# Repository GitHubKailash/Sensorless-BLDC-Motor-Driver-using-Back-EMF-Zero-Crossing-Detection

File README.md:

# Sensorless BLDC Motor Drive

<p align="center">
  <b>A Low-Cost Sensorless Three-Phase BLDC Motor Controller Using Arduino UNO, IR2104S Gate Drivers, and MOSFET-Based Power Electronics</b>
</p>

---

# Overview

The **Sensorless BLDC Motor Drive** is an Arduino UNO-based three-phase Brushless DC (BLDC) motor controller designed to operate a BLDC motor without requiring external Hall-effect position sensors.

The system uses **Back Electromotive Force (BEMF) zero-crossing detection** to determine the rotor position and perform electronic commutation. An Arduino UNO processes the BEMF signals and generates the required PWM control signals to operate six power MOSFETs through three IR2104S half-bridge gate driver ICs.

The controller implements a six-step electronic commutation technique to drive the three-phase BLDC motor. Motor speed is controlled using PWM, with dedicated push buttons for increasing and decreasing the motor speed.

The project was initially implemented and tested on a perfboard to verify the hardware functionality. Following successful prototype development, the complete motor driver circuit was designed as a PCB using **KiCad**, providing a dedicated hardware implementation.

The project focuses on developing an affordable, compact, and sensorless BLDC motor controller while exploring embedded systems, power electronics, motor control algorithms, and PCB design.

---

# Problem Statement

Conventional sensored BLDC motor controllers require Hall-effect sensors to determine the rotor position for electronic commutation.

Although these sensors provide rotor position information, they increase hardware complexity, wiring requirements, and overall system cost.

This project addresses these limitations by developing a sensorless BLDC motor controller that estimates rotor position using the Back Electromotive Force generated in the motor windings.

By eliminating the need for external rotor position sensors, the system reduces hardware requirements while implementing electronic commutation and PWM-based speed control using an Arduino UNO.

---

# Project Objectives

- Develop a sensorless BLDC motor controller using Arduino UNO.
- Implement BEMF-based rotor position detection.
- Perform six-step electronic commutation.
- Design a three-phase MOSFET inverter circuit.
- Interface IR2104S gate drivers with the Arduino controller.
- Implement PWM-based motor speed control.
- Provide manual speed adjustment using push buttons.
- Develop and test the complete circuit on a perfboard.
- Design a dedicated PCB using KiCad.
- Understand the practical implementation of embedded motor control and power electronics.

---

# Key Features

- Sensorless BLDC motor operation.
- Back EMF zero-crossing detection.
- Six-step electronic commutation.
- Three-phase inverter architecture.
- Arduino UNO-based control system.
- Three IR2104S half-bridge gate drivers.
- Six N-channel power MOSFETs.
- PWM-based speed control.
- Manual speed adjustment using push buttons.
- Open-loop startup sequence.
- Closed-loop BEMF-based commutation after startup.
- Perfboard-based hardware prototype.
- Custom PCB schematic and design using KiCad.

---

# System Architecture

The system consists of an Arduino-based control unit, a three-phase MOSFET inverter, gate driver circuits, and a sensorless BLDC motor.

```text
                  12V DC SUPPLY
                       |
                       |
              +------------------+
              |  Power Inverter  |
              |                  |
              |  6 Power MOSFETs |
              +------------------+
                       |
                       |
              +------------------+
              |  Three-Phase     |
              |  BLDC Motor      |
              +------------------+
                       |
             Phase A, B and C
                       |
                       v
              +------------------+
              |  BEMF Detection  |
              |  Voltage Divider |
              |  Network         |
              +------------------+
                       |
                       v
              +------------------+
              |   Arduino UNO    |
              |   ATmega328P     |
              |                  |
              |  BEMF Detection  |
              |  Commutation     |
              |  PWM Generation  |
              |  Speed Control   |
              +------------------+
                       |
                       v
              +------------------+
              |  IR2104S Gate    |
              |  Driver ICs      |
              +------------------+
                       |
                       v
              +------------------+
              |  MOSFET Switching|
              |  Control         |
              +------------------+
                       |
                       v
                 BLDC Motor
```

### Main System Blocks

| Block | Function |
|---|---|
| Arduino UNO | Main controller and commutation logic |
| BEMF Detection Network | Detects rotor position using motor-generated voltage |
| IR2104S Gate Drivers | Drive high-side and low-side MOSFETs |
| MOSFET Inverter | Converts DC supply into three-phase switched output |
| BLDC Motor | Converts electrical energy into mechanical rotation |
| Speed Control Buttons | Increase and decrease motor speed |

---

# Working Principle

The controller operates using the Back Electromotive Force generated by the three motor windings.

Unlike sensored BLDC controllers, this system does not depend on Hall-effect sensors to determine rotor position.

## 1. Back EMF Generation

When a BLDC motor rotates, its stator windings generate Back Electromotive Force (BEMF).

The three motor phases generate BEMF waveforms that are electrically displaced by 120 degrees.

During six-step commutation:

- Two motor phases are energized.
- One motor phase remains floating.
- The floating phase is monitored for BEMF zero crossing.

The zero-crossing information is used to determine the appropriate time for the next commutation event.

## 2. Virtual Neutral Point Generation

Three resistors are connected to the three motor phases to generate a virtual neutral reference point.

This reference voltage is compared with the BEMF voltage of the floating motor phase.

The voltage divider network reduces the motor phase voltage to a suitable level for the Arduino's detection circuitry.

## 3. BEMF Zero-Crossing Detection

The Arduino UNO uses its internal analog comparator to detect the zero-crossing events.

The comparator compares:

- Positive input: Virtual neutral reference.
- Negative input: Selected floating-phase BEMF signal.

When the floating-phase BEMF crosses the virtual neutral voltage, the comparator output changes state.

The Arduino detects this transition using the analog comparator interrupt.

## 4. Six-Step Electronic Commutation

The motor is controlled using six-step electronic commutation.

During each commutation step, one high-side MOSFET and one low-side MOSFET are activated while the third phase remains floating.

| Step | High-Side MOSFET | Low-Side MOSFET | Floating Phase |
|---|---|---|---|
| 1 | A | B | C |
| 2 | A | C | B |
| 3 | B | C | A |
| 4 | B | A | C |
| 5 | C | A | B |
| 6 | C | B | A |

The sequence repeats continuously to maintain motor rotation.

## 5. Open-Loop Startup

At standstill, the motor does not generate sufficient BEMF for reliable rotor position detection.

Therefore, the controller initially uses an open-loop startup sequence.

During startup:

1. The Arduino initializes the PWM output.
2. A predefined commutation sequence is applied.
3. The commutation interval gradually decreases.
4. The motor accelerates.
5. Once sufficient BEMF is available, the controller enables comparator interrupt-based commutation.

## 6. PWM-Based Speed Control

Motor speed is controlled by adjusting the PWM duty cycle applied to the gate driver control signals.

Two push buttons are provided:

- **Speed Up:** Increases the PWM duty cycle.
- **Speed Down:** Decreases the PWM duty cycle.

The controller maintains the duty cycle within predefined minimum and maximum limits.

---

# Hardware Components

| S.No | Component | Quantity | Purpose |
|---|---|---:|---|
| 1 | Arduino UNO | 1 | Main controller |
| 2 | IR2104S Gate Driver IC | 3 | Half-bridge gate driving |
| 3 | N-Channel Power MOSFET | 6 | Three-phase inverter |
| 4 | 1N4148 Diode | 3 | Bootstrap charging |
| 5 | 33kΩ Resistor | 6 | BEMF sensing and virtual neutral network |
| 6 | 10kΩ Resistor | 3 | Voltage divider network |
| 7 | 100Ω Resistor | 6 | MOSFET gate resistors |
| 8 | 10µF Capacitor | 3 | Gate driver supply decoupling |
| 9 | 2.2µF Capacitor | 3 | Bootstrap capacitors |
| 10 | Push Buttons | 2 | Speed adjustment |
| 11 | BLDC Motor | 1 | Motor load |
| 12 | 12V DC Supply | 1 | Power source |
| 13 | Perfboard | 1 | Prototype implementation |
| 14 | PCB | 1 | Custom circuit implementation |

**Note:** The MOSFET part number should be finalized according to the actual hardware revision. The supplied original reference schematic shows 06N03LA, while your KiCad schematic shows IRF3205.

---

# Controller and Pin Configuration

The Arduino UNO uses its ATmega328P microcontroller for PWM generation, BEMF detection, and motor commutation.

| Arduino Pin | Function |
|---|---|
| D3 | Phase A control |
| D4 | Phase B control |
| D5 | Phase C control |
| D6 | Virtual neutral reference (AIN0) |
| D7 | Phase A BEMF detection (AIN1) |
| A2 | Phase B BEMF detection |
| A3 | Phase C BEMF detection |
| D9 | Phase A gate driver PWM/SD control |
| D10 | Phase B gate driver PWM/SD control |
| D11 | Phase C gate driver PWM/SD control |
| A0 | Speed Up button |
| A1 | Speed Down button |

---

# Gate Driver Circuit

The project uses three IR2104S half-bridge gate driver ICs to control the six MOSFETs.

Each IR2104S controls one motor phase and provides:

- High-side MOSFET gate control.
- Low-side MOSFET gate control.
- Bootstrap-based high-side gate drive.
- Independent gate driver supply and switching connections.

The three gate driver circuits are connected to the corresponding Phase A, Phase B, and Phase C inverter stages.

Each phase consists of:

- One high-side N-channel MOSFET.
- One low-side N-channel MOSFET.
- One IR2104S gate driver.
- Associated bootstrap and gate resistor components.

---

# Software Implementation

The firmware is developed using the Arduino IDE in Embedded C/C++.

The program implements the following functions:

1. GPIO initialization.
2. PWM timer configuration.
3. Analog comparator configuration.
4. Initial open-loop motor startup.
5. BEMF zero-crossing detection.
6. Interrupt-based commutation.
7. Six-step switching sequence.
8. PWM duty cycle adjustment.
9. Push-button speed control.

### PWM Generation

The Arduino UNO uses its hardware timers to generate PWM signals.

The PWM outputs are configured on:

- Pin 9 – Phase A.
- Pin 10 – Phase B.
- Pin 11 – Phase C.

The PWM duty cycle is adjusted according to the selected motor speed.

### BEMF Interrupt Handling

The analog comparator interrupt detects the rising and falling transitions of the selected floating motor phase.

Based on the detected transition, the firmware advances the commutation sequence.

This allows the motor controller to synchronize its switching sequence with the rotor's electrical position once the motor reaches sufficient speed.

---

# Motor Speed Control

The motor speed is controlled by modifying the PWM duty cycle.

The firmware uses two push buttons connected to the Arduino UNO.

| Parameter | Configuration |
|---|---|
| Speed Up | A0 |
| Speed Down | A1 |
| Minimum PWM Duty | 50 |
| Maximum PWM Duty | 255 |
| PWM Resolution | 8-bit |
| Initial PWM Duty | 150 |

The initial PWM value and speed limits can be adjusted in the firmware according to the motor and power-stage characteristics.

---

# Hardware Development

The project was developed through two major hardware implementation stages.

## Stage 1: Perfboard Prototype

The initial motor controller was implemented on a perfboard.

The complete circuit, including the Arduino interface, gate driver ICs, MOSFET switching stages, and BEMF sensing network, was assembled and tested.

The purpose of this stage was to:

- Verify circuit connections.
- Test the gate driver operation.
- Validate MOSFET switching.
- Verify motor startup.
- Test BEMF-based commutation.
- Evaluate PWM speed control.

**Prototype Images:**

Add your actual perfboard photographs below.

## Stage 2: PCB Design Using KiCad

After developing the working prototype, the motor driver circuit was designed as a dedicated PCB using KiCad.

The PCB design integrates the three half-bridge gate driver stages and the associated MOSFET power switching circuitry.

### PCB Design Process

1. Circuit schematic development.
2. Component selection.
3. Schematic symbol placement.
4. Electrical connection and net assignment.
5. PCB footprint assignment.
6. PCB component placement.
7. Track routing.
8. Design Rule Check (DRC).
9. PCB visualization and fabrication preparation.

### KiCad Schematic

Add your exported KiCad schematic here.

### PCB Layout

Add your PCB layout screenshot here.

### 3D PCB Model

Add your KiCad 3D viewer screenshot here.

---

# Circuit Diagram

The motor controller consists of three identical half-bridge stages.

Each stage drives one motor phase.

The complete system includes:

- Arduino UNO control circuit.
- Three IR2104S gate driver circuits.
- Six MOSFET switching devices.
- BEMF sensing voltage divider network.
- Virtual neutral reference network.
- Speed control push buttons.
- DC power supply.

---

# Testing and Validation

The developed prototype is evaluated through the following testing procedures.

| Test | Objective |
|---|---|
| Power Supply Test | Verify the DC supply and gate driver supply |
| Gate Driver Test | Check high-side and low-side gate control |
| MOSFET Switching Test | Verify inverter switching operation |
| Motor Startup Test | Evaluate open-loop startup |
| BEMF Detection Test | Verify floating-phase zero-crossing detection |
| Commutation Test | Validate the six-step switching sequence |
| Speed Control Test | Verify speed increment and decrement |
| PCB Design Validation | Check schematic connectivity and PCB design rules |

### Expected Observations

- The motor should start using the initial open-loop commutation sequence.
- BEMF zero crossings should be detected after sufficient motor rotation.
- The controller should perform six-step commutation.
- Increasing PWM duty should increase motor speed within the operating range.
- Decreasing PWM duty should reduce motor speed.

Add your measured test results, oscilloscope waveforms, and motor performance observations here.

---

# Applications

- Drone propulsion systems.
- Small electric propulsion systems.
- Robotics.
- Electric vehicle research prototypes.
- Industrial motor control experiments.
- Embedded motor control applications.
- Educational power electronics projects.
- DIY electronic speed controllers.

---

# Future Improvements

The project can be further developed through the following improvements:

- Closed-loop RPM measurement and display.
- LCD-based real-time motor parameter monitoring.
- ESP32-based wireless monitoring.
- Blynk IoT dashboard integration.
- Motor temperature monitoring.
- Overcurrent protection.
- Undervoltage protection.
- MOSFET thermal protection.
- Improved startup reliability.
- Optimized PCB layout and thermal management.
- Improved motor speed regulation.
- Advanced motor control algorithms.

---

# Safety Considerations

- Verify all circuit connections before applying power.
- Use a current-limited DC supply during initial testing.
- Ensure adequate MOSFET and gate driver ratings.
- Provide sufficient PCB copper area and thermal management.
- Avoid short circuits between motor phases.
- Verify gate drive waveforms before connecting the motor.
- Use suitable protection against supply transients.
- Disconnect the power supply before modifying the circuit.

---

# Repository Structure

```text
Sensorless-BLDC-Motor-Drive/
│
├── README.md
│
├── Arduino_Code/
│   └── Sensorless_BLDC_Controller/
│       └── Sensorless_BLDC_Controller.ino
│
├── Circuit_Diagram/
│   ├── circuit_diagram.png
│   └── circuit_schematic.pdf
│
├── PCB_Design/
│   ├── KiCad_Project/
│   ├── Gerber_Files/
│   ├── pcb_layout.png
│   ├── pcb_3d.png
│   └── kicad_schematic.png
│
├── Hardware_Prototype/
│   ├── perfboard_top.jpg
│   ├── perfboard_side.jpg
│   └── motor_testing.jpg
│
├── Testing_Results/
│   ├── bemf_waveforms/
│   └── motor_testing/
│
└── Datasheets/
    ├── Arduino_UNO.pdf
    ├── IR2104S.pdf
    └── MOSFET_Datasheet.pdf
```

---

# Technologies Used

| Category | Technology |
|---|---|
| Microcontroller | Arduino UNO |
| Programming Language | Embedded C/C++ |
| Development Environment | Arduino IDE |
| Gate Driver | IR2104S |
| Power Electronics | N-Channel MOSFETs |
| PCB Design | KiCad |
| Motor Control Technique | Six-Step Commutation |
| Rotor Position Detection | BEMF Zero-Crossing Detection |
| Speed Control | PWM |

---

# License

This project is licensed under the MIT License.

See the [LICENSE](LICENSE) file for details.

---

# Author

**Kailash S**

Electrical and Electronics Engineering  
Chennai Institute of Technology

**Areas of Interest:**

- Embedded Systems
- Power Electronics
- BLDC Motor Control
- PCB Design
- Arduino and Microcontrollers
- IoT and Robotics
- Drone Technology

---

<p align="center">
  <b>Sensorless BLDC Motor Drive</b>
  <br>
  Designed and developed using Arduino UNO, power electronics, and KiCad.
  <br><br>
  ⭐ If you find this project useful, consider giving this repository a star!
</p>

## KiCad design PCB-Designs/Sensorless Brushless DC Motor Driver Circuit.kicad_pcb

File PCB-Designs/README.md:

# Sensorless BLDC Motor Drive – 4-Layer PCB Design

## Project Overview

This project focuses on the design and development of a **Sensorless Brushless DC (BLDC) Motor Drive** using a custom-designed 4-layer PCB. The system is designed to control BLDC motor operation without requiring Hall-effect sensors by utilizing Back Electromotive Force (Back-EMF) detection.

The controller integrates the microcontroller and three-phase motor driver circuitry onto a single PCB, providing a compact and integrated motor control solution.

## Key Features

- Sensorless BLDC motor control using Back-EMF detection.
- Three-phase inverter-based motor driving circuit.
- Integrated microcontroller-based control system.
- Four-layer PCB design for improved routing and power distribution.
- USB-based programming interface.
- 12V DC power supply.
- Designed for A2212 13T 1000KV BLDC motor.

## Hardware Specifications

| Parameter | Specification |
|---|---|
| Motor Type | Brushless DC Motor |
| Motor Model | A2212 13T |
| Motor Speed Constant | 1000 KV |
| Operating Supply | 12V DC |
| Control Technique | Sensorless Control |
| Feedback Method | Back-EMF Detection |
| PCB Layers | 4 Layers |
| Design Software | KiCad |

## PCB Design

The PCB is designed using KiCad with a four-layer architecture to accommodate the control circuitry, power electronics, and signal routing.

The four-layer structure provides:
- Improved power and ground distribution.
- Better signal routing.
- Reduced interference between control and power sections.
- Compact component integration.

## Working Principle

1. The microcontroller generates the switching signals required for three-phase motor operation.
2. The inverter circuit drives the BLDC motor through its three-phase windings.
3. Back-EMF signals are monitored from the non-energized motor phase.
4. Zero-crossing detection is used to determine rotor position.
5. The controller performs electronic commutation based on the detected rotor position.
6. This process continues to maintain motor rotation without Hall-effect sensors.

## Tools and Technologies

- KiCad – Schematic Capture and PCB Design
- Embedded C / Arduino IDE – Firmware Development
- Back-EMF Detection – Sensorless Rotor Position Estimation
- Four-Layer PCB Technology – Hardware Implementation

## Repository Contents

- `Schematic/` – Circuit schematic files
- `PCB/` – Four-layer PCB layout files
- `Gerber/` – PCB manufacturing files
- `BOM/` – Bill of Materials
- `Images/` – PCB layout and design images
- `README.md` – Project documentation

## Applications

- Drone BLDC motor drives
- Robotics and automation
- Electric propulsion systems
- Embedded motor control applications

## Future Improvements

- Closed-loop speed regulation.
- Improved startup and low-speed performance.
- Current and temperature monitoring.
- Protection against overcurrent and undervoltage.
- PCB testing and performance optimization.

## Author

Designed and developed as an Electrical and Electronics Engineering project.

**Project:** Sensorless BLDC Motor Drive  
**PCB Design:** 4-Layer Custom PCB  
**Design Tool:** KiCad

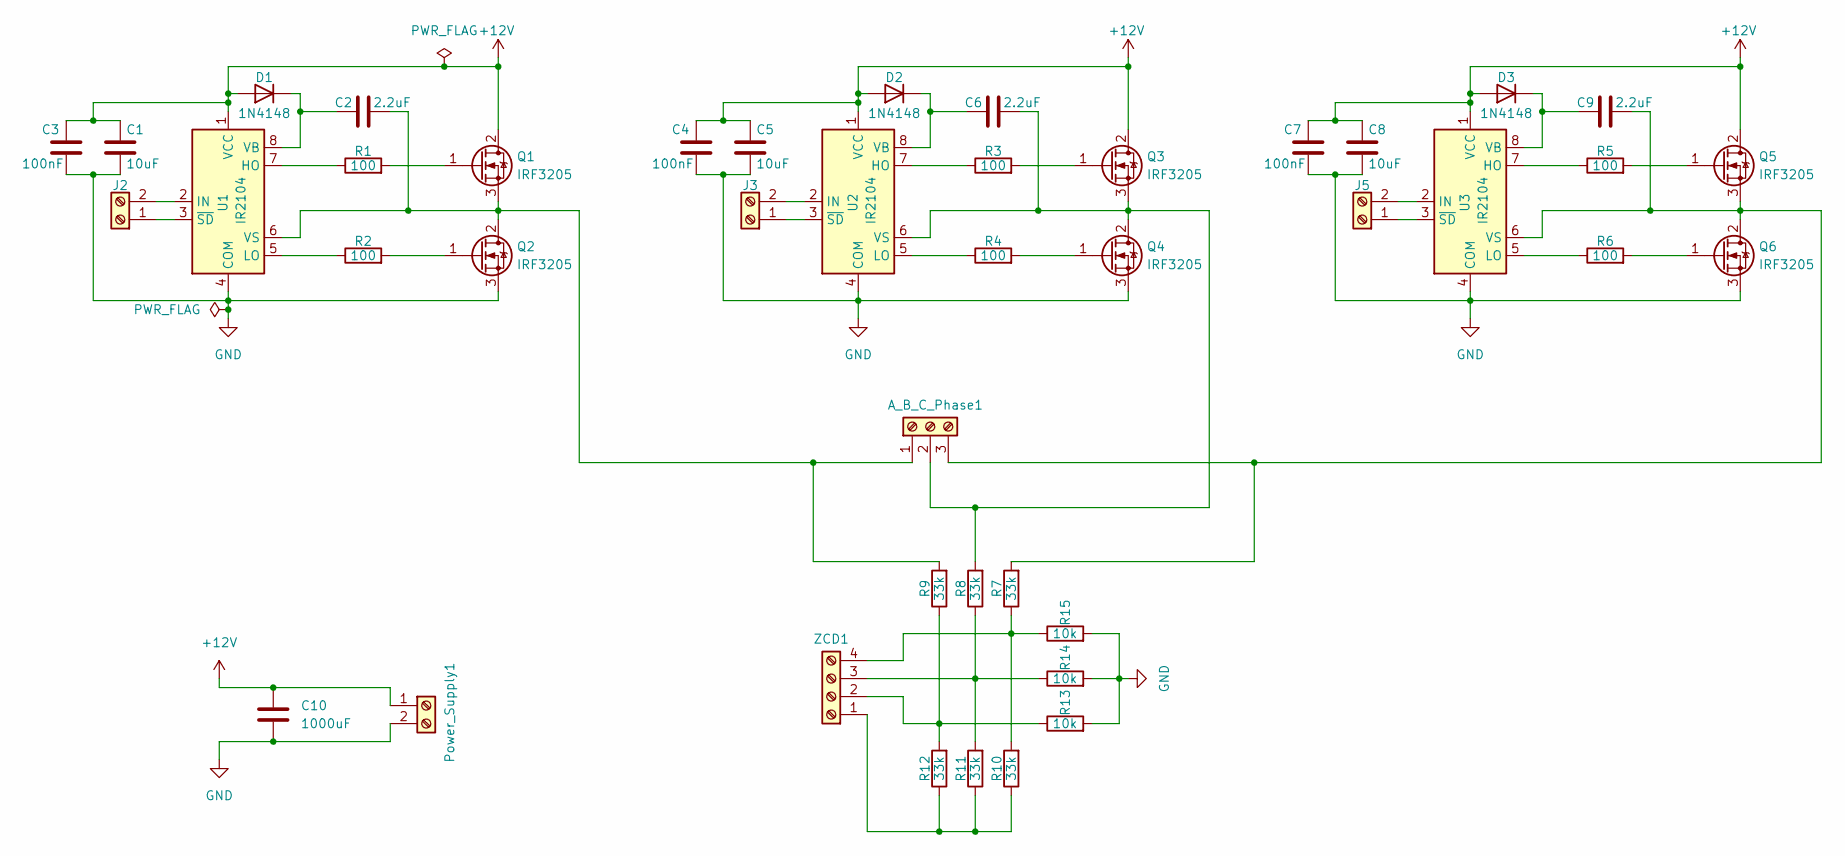
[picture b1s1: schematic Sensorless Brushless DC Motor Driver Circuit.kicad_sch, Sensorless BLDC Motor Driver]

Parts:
A_B_C_Phase1: Screw_Terminal_01x03; Altech_AK300_1x03_P5.00mm_45-Degree
C1, C5, C8: 10uF; C_Elec_5x5.8
C2, C6, C9: 2.2uF; C_Elec_5x5.8
C3, C4, C7: 100nF; C_0805_2012Metric
C10: 1000uF; C_Radial_D10.0mm_H16.0mm_P5.00mm
D1, D2, D3: 1N4148; D_DO-35_SOD27_P7.62mm_Horizontal
J2, J3, J5: Screw_Terminal_01x02; Altech_AK300_1x02_P5.00mm_45-Degree
Power_Supply1: Screw_Terminal_01x02; Altech_AK300_1x02_P5.00mm_45-Degree
Q1, Q2, Q3, Q4, Q5, Q6: IRF3205; TO-220-3_Vertical
R1, R2, R3, R4, R5, R6: 100; R_0805_2012Metric
R7, R8, R9, R10, R11, R12: 33k; R_0805_2012Metric
R13, R14, R15: 10k; R_0805_2012Metric
U1, U2, U3: IR2104; SOIC-8_3.9x4.9mm_P1.27mm
ZCD1: Screw_Terminal_01x04; Altech_AK300_1x04_P5.00mm_45-Degree

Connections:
+12V: C1.2, C3.1, C4.1, C5.2, C7.1, C8.2, C10.1, D1.2 (A), D2.2 (A), D3.2 (A), Power_Supply1.1, Q1.2 (D), Q3.2 (D), Q5.2 (D), U1.1 (VCC), U2.1 (VCC), U3.1 (VCC)
GND: C1.1, C3.2, C4.2, C5.1, C7.2, C8.1, C10.2, Power_Supply1.2, Q2.3 (S), Q4.3 (S), Q6.3 (S), R13.2, R14.2, R15.2, U1.4 (COM), U2.4 (COM), U3.4 (COM)
unnamed: A_B_C_Phase1.1, C2.2, Q1.3 (S), Q2.2 (D), R9.2, U1.6 (VS)
unnamed: A_B_C_Phase1.2, C6.2, Q3.3 (S), Q4.2 (D), R8.2, U2.6 (VS)
unnamed: A_B_C_Phase1.3, C9.2, Q5.3 (S), Q6.2 (D), R7.2, U3.6 (VS)
unnamed: C2.1, D1.1 (K), U1.8 (VB)
unnamed: C6.1, D2.1 (K), U2.8 (VB)
unnamed: C9.1, D3.1 (K), U3.8 (VB)
unnamed: J2.1, U1.3 (~SD)
unnamed: J2.2, U1.2 (IN)
unnamed: J3.1, U2.3 (~SD)
unnamed: J3.2, U2.2 (IN)
unnamed: J5.1, U3.3 (~SD)
unnamed: J5.2, U3.2 (IN)
unnamed: Q1.1 (G), R1.2
unnamed: Q2.1 (G), R2.2
unnamed: Q3.1 (G), R3.2
unnamed: Q4.1 (G), R4.2
unnamed: Q5.1 (G), R5.2
unnamed: Q6.1 (G), R6.2
unnamed: R1.1, U1.7 (HO)
unnamed: R2.1, U1.5 (LO)
unnamed: R3.1, U2.7 (HO)
unnamed: R4.1, U2.5 (LO)
unnamed: R5.1, U3.7 (HO)
unnamed: R6.1, U3.5 (LO)
unnamed: R10.1, R11.1, R12.1, ZCD1.1
unnamed: R9.1, R12.2, R13.1, ZCD1.2
unnamed: R8.1, R11.2, R14.1, ZCD1.3
unnamed: R7.1, R10.2, R15.1, ZCD1.4

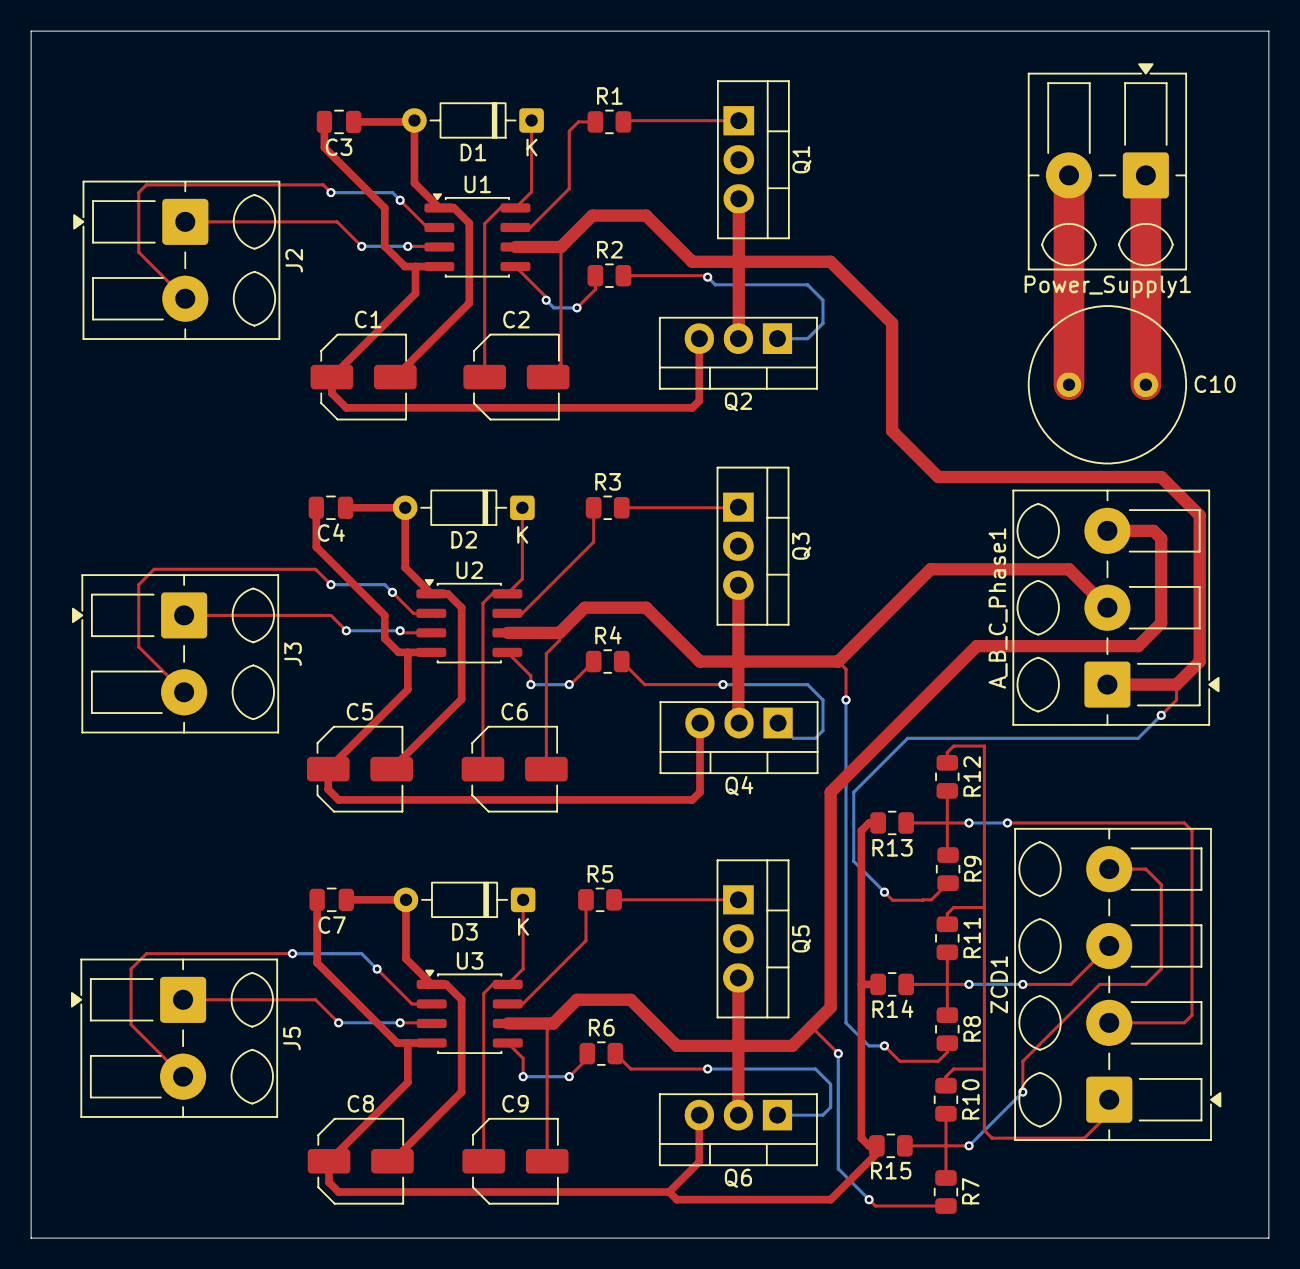
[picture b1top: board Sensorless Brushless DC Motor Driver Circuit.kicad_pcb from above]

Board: 4 copper layers, 80.5 x 78.5 mm, 43 parts (0 on the bottom side), 30 nets.

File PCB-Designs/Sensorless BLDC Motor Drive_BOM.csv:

"Reference","Qty","Value","DNP","Exclude from BOM","Exclude from Board","Exclude from Simulation","Exclude from Position Files","Footprint","Datasheet"
"A_B_C_Phase1","1","Screw_Terminal_01x03","","","","","${EXCLUDE_FROM_POS_FILES}","TerminalBlock_Altech:Altech_AK300_1x03_P5.00mm_45-Degree",""
"C1,C5,C8","3","10uF","","","","","${EXCLUDE_FROM_POS_FILES}","Capacitor_SMD:C_Elec_5x5.8",""
"C2,C6,C9","3","2.2uF","","","","","${EXCLUDE_FROM_POS_FILES}","Capacitor_SMD:C_Elec_5x5.8",""
"C3,C4,C7","3","100nF","","","","","${EXCLUDE_FROM_POS_FILES}","Capacitor_SMD:C_0805_2012Metric",""
"C10","1","1000uF","","","","","${EXCLUDE_FROM_POS_FILES}","Capacitor_THT:C_Radial_D10.0mm_H16.0mm_P5.00mm",""
"D1,D2,D3","3","1N4148","","","","","${EXCLUDE_FROM_POS_FILES}","Diode_THT:D_DO-35_SOD27_P7.62mm_Horizontal","https://assets.nexperia.com/documents/data-sheet/1N4148_1N4448.pdf"
"J2,J3,J5,Power_Supply1","4","Screw_Terminal_01x02","","","","","${EXCLUDE_FROM_POS_FILES}","TerminalBlock_Altech:Altech_AK300_1x02_P5.00mm_45-Degree",""
"Q1,Q2,Q3,Q4,Q5,Q6","6","IRF3205","","","","","${EXCLUDE_FROM_POS_FILES}","Package_TO_SOT_THT:TO-220-3_Vertical","http://www.irf.com/product-info/datasheets/data/irf3205.pdf"
"R1,R2,R3,R4,R5,R6","6","100","","","","","${EXCLUDE_FROM_POS_FILES}","Resistor_SMD:R_0805_2012Metric",""
"R7,R8,R9,R10,R11,R12","6","33k","","","","","${EXCLUDE_FROM_POS_FILES}","Resistor_SMD:R_0805_2012Metric",""
"R13,R14,R15","3","10k","","","","","${EXCLUDE_FROM_POS_FILES}","Resistor_SMD:R_0805_2012Metric",""
"U1,U2,U3","3","IR2104","","","","","${EXCLUDE_FROM_POS_FILES}","Package_SO:SOIC-8_3.9x4.9mm_P1.27mm","https://www.infineon.com/dgdl/ir2104.pdf?fileId=5546d4625336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"
"ZCD1","1","Screw_Terminal_01x04","","","","","${EXCLUDE_FROM_POS_FILES}","TerminalBlock_Altech:Altech_AK300_1x04_P5.00mm_45-Degree",""
